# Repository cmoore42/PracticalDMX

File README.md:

# PracticalDMX
A battery powered standalone sACN node for remotely running on-stage practical lights.

The inspiration for this project came from a show I worked on that required lights on a moving platform.  
The lights were "practicals" - lights on stage that need to look like real world lights.
This is usually done by having the lights controlled by the lighting console, and having the console operator take
a cue to turn on the light when an actor flips a non-functional switch.
However, in this case, the lights were on moving platforms so couldn't be wired to either power or control.
The solution was a battery powered system with a 12V lead acid battery, a switch, and a 2W 12V light fixture.  
This meant that the actors had to actually flip a real switch to turn on the light.

This project is an sACN version of that.  It's a module that is powered by a 12V battery, can run 12V lights, 
but appears as an sACN node.
The lights can be completely portable, but can be controlled by a lighting console.

# Software
- Network configuration using WiFiManager
- sACN receive functionality using E131 library

# Hardware
- NodeMCU Devkit
- 0.96" I2C OLED display (From DIYMall)
- Custom PCB
- Four FQP30N06L N-Channel MOSFETs (From Sparkfun)
- Four 10K resistors
- Various connectors, headers, sockets

# Project Status
- PC Board designed and ordered
- PC Board built and tested with 12V input power
- Software done and tested, as much as possible without hardware

# To Do List
- Add code to allow for setting of universe and address offset
- Test PC board with actual 12V LED lights
- Add overcurrent protection to circuit
- Create 3D printable case

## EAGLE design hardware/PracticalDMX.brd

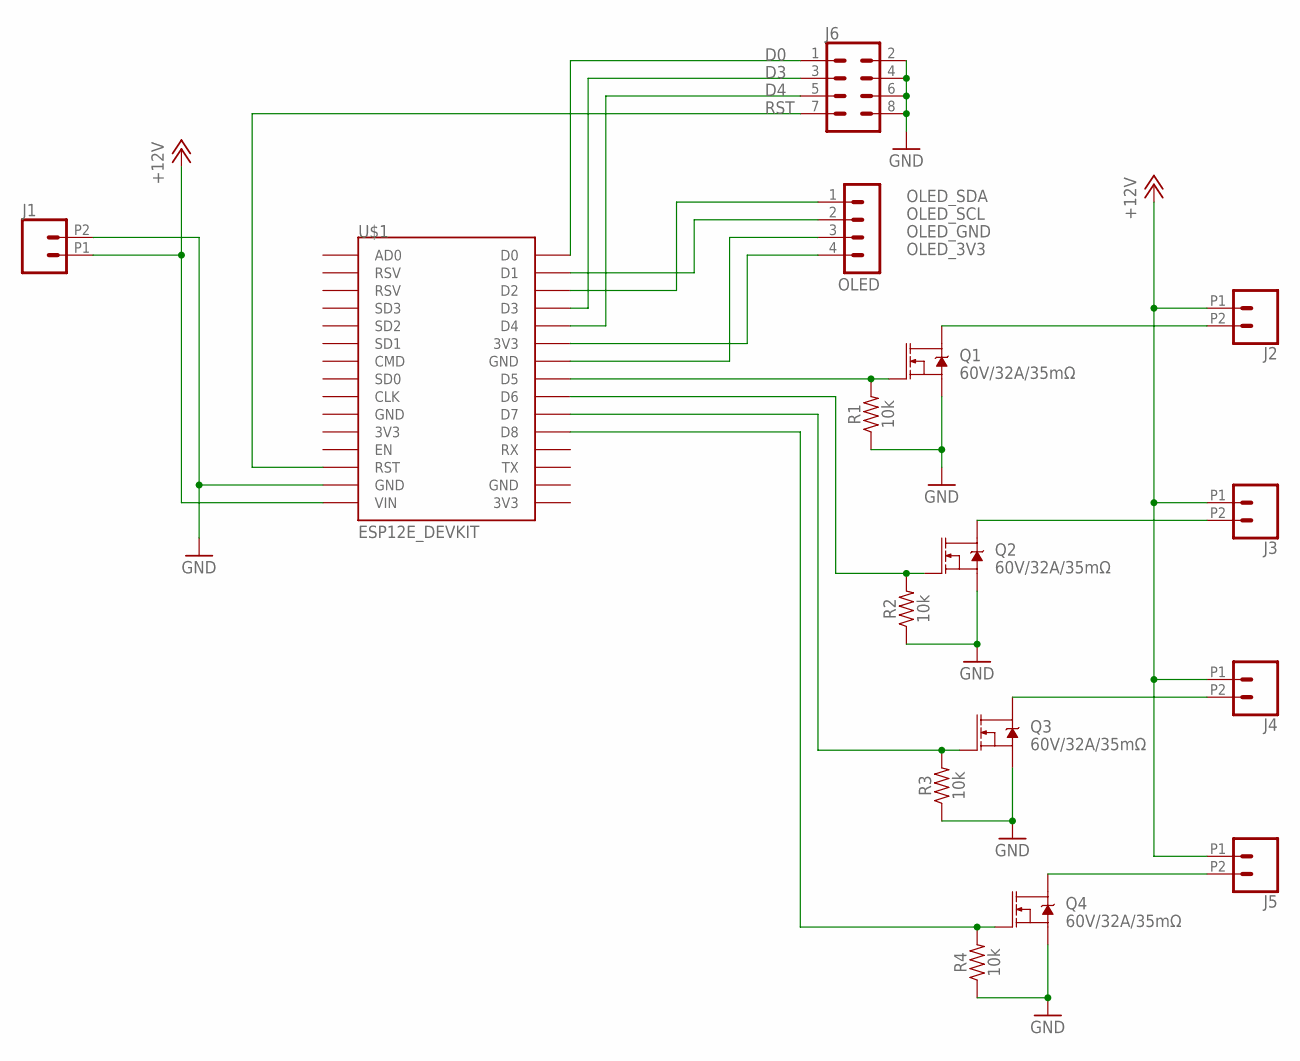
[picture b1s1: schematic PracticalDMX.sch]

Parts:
J1, J2, J3, J4, J5: CONN_022.54MM_SCREWTERM; 1X02_2.54_SCREWTERM
J6: CONN_04X2; 2X4
OLED: MA04-1
Q1, Q2, Q3, Q4: 60V/32A/35mΩ; TO220V
R1, R2, R3, R4: 10k; AXIAL-0.3
U$1: ESP12E_DEVKIT

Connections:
+12V: J1.P1 (1), J2.P1 (1), J3.P1 (1), J4.P1 (1), J5.P1 (1), U$1.VIN
D0: J6.1, U$1.D0
D3: J6.3, U$1.D3
D4: J6.5, U$1.D4
GND: J1.P2 (2), J6.2, J6.4, J6.6, J6.8, Q1.3 (S), Q2.3 (S), Q3.3 (S), Q4.3 (S), R1.P$1 (1), R2.P$1 (1), R3.P$1 (1), R4.P$1 (1), U$1.GND@1 (GND)
unnamed: J5.P2 (2), Q4.2 (D)
unnamed: J4.P2 (2), Q3.2 (D)
unnamed: Q1.1 (G), R1.P$2 (2), U$1.D5
unnamed: Q2.1 (G), R2.P$2 (2), U$1.D6
unnamed: Q3.1 (G), R3.P$2 (2), U$1.D7
unnamed: Q4.1 (G), R4.P$2 (2), U$1.D8
unnamed: J3.P2 (2), Q2.2 (D)
unnamed: J2.P2 (2), Q1.2 (D)
OLED_3V3: OLED.4, U$1.3V3@1 (3V3)
OLED_GND: OLED.3, U$1.GND@2 (GND)
OLED_SCL: OLED.2, U$1.D1
OLED_SDA: OLED.1, U$1.D2
RST: J6.7, U$1.RST

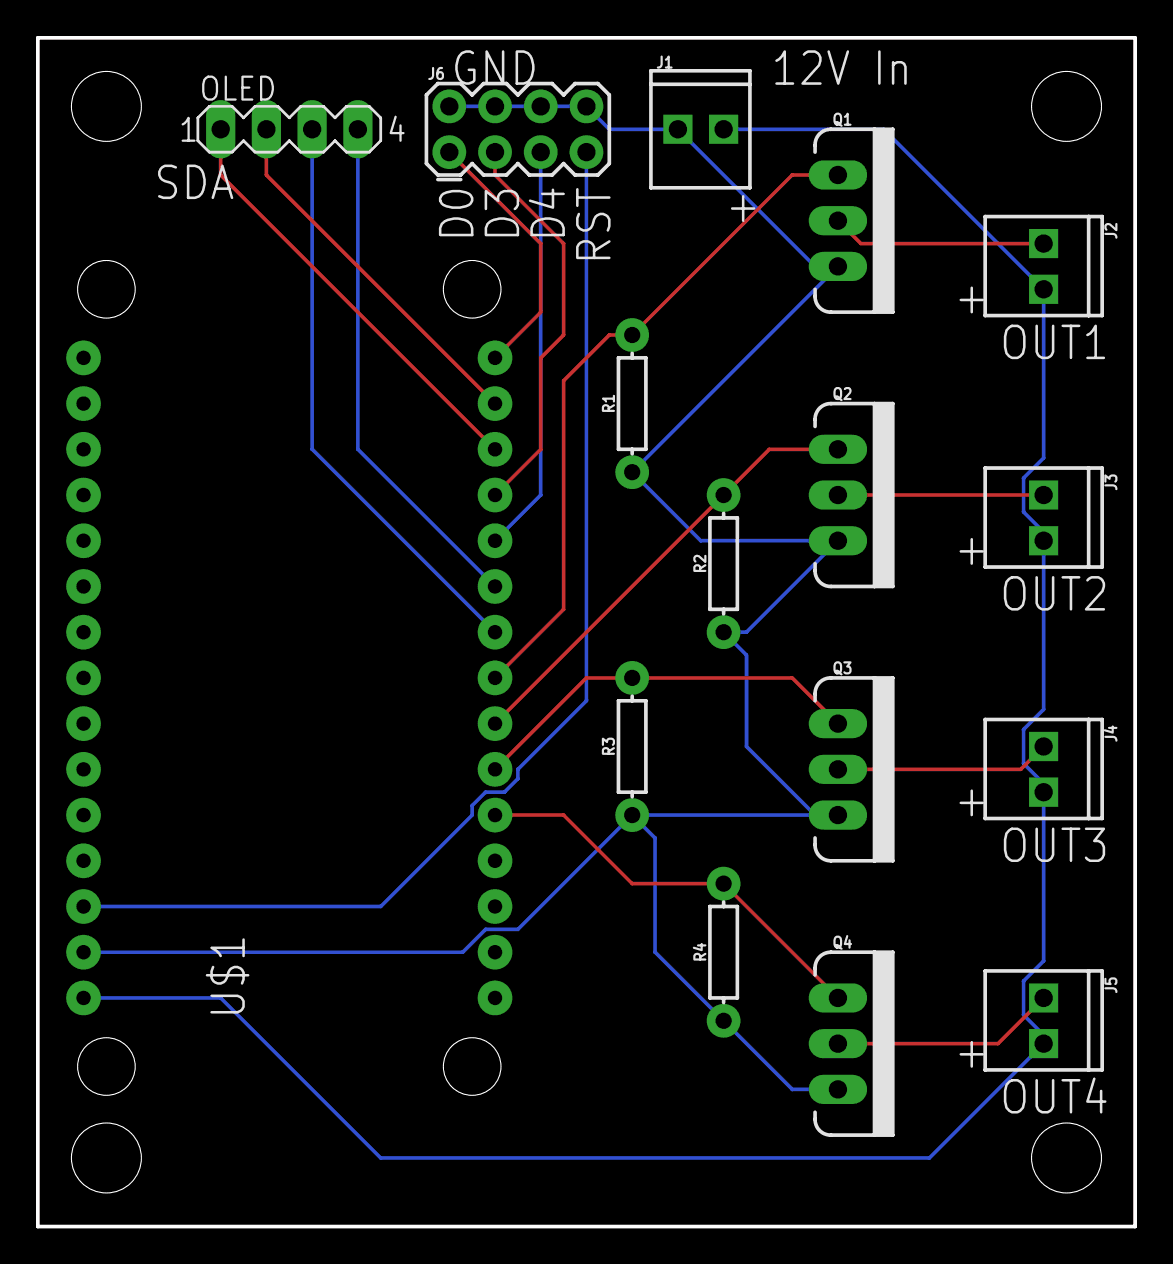
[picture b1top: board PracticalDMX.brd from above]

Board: 2 copper layers, 61.0 x 66.0 mm, 16 parts (0 on the bottom side), 18 nets.

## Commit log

2018-07-06 Initial checkin of code, schematic, and board layout.
2018-07-07 Added license file.
2018-07-07 Added license info to .ino file. Did some code and comment cleanup.
2018-07-13 Cleaned up some of the state machine code. Moved some functionality to the state_change() code. For example, enabling the E13.1 listener now happens when we change state to CONNECTED. Same with the L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
2018-07-13 First part of REST server. Responds to GET request for /offset and /universe. Still need to implement PUTs.
2018-07-13 Removed a couple of debug prints.
2018-07-15 Improved universe and channel_offset handling. Display now shows universe/address, accounting for the offset. E13.1 listener now listens for the right universe.
2018-07-16 Changed channel_offset to base_address. To better align with the typical "set the DMX address" concept, I'm now using base_address (the first DMX address in the set) rather than channel_offset (a val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
2018-07-24 Fixed logic when configuring for the first time. The logic was incorrect for the case where there was no WiFi data at all.

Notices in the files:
parts and their libraries:
SparkFun-Connectors: Licensing: Creative Commons ShareAlike 4.0 International - https://creativecommons.org/licenses/by-sa/4.0
